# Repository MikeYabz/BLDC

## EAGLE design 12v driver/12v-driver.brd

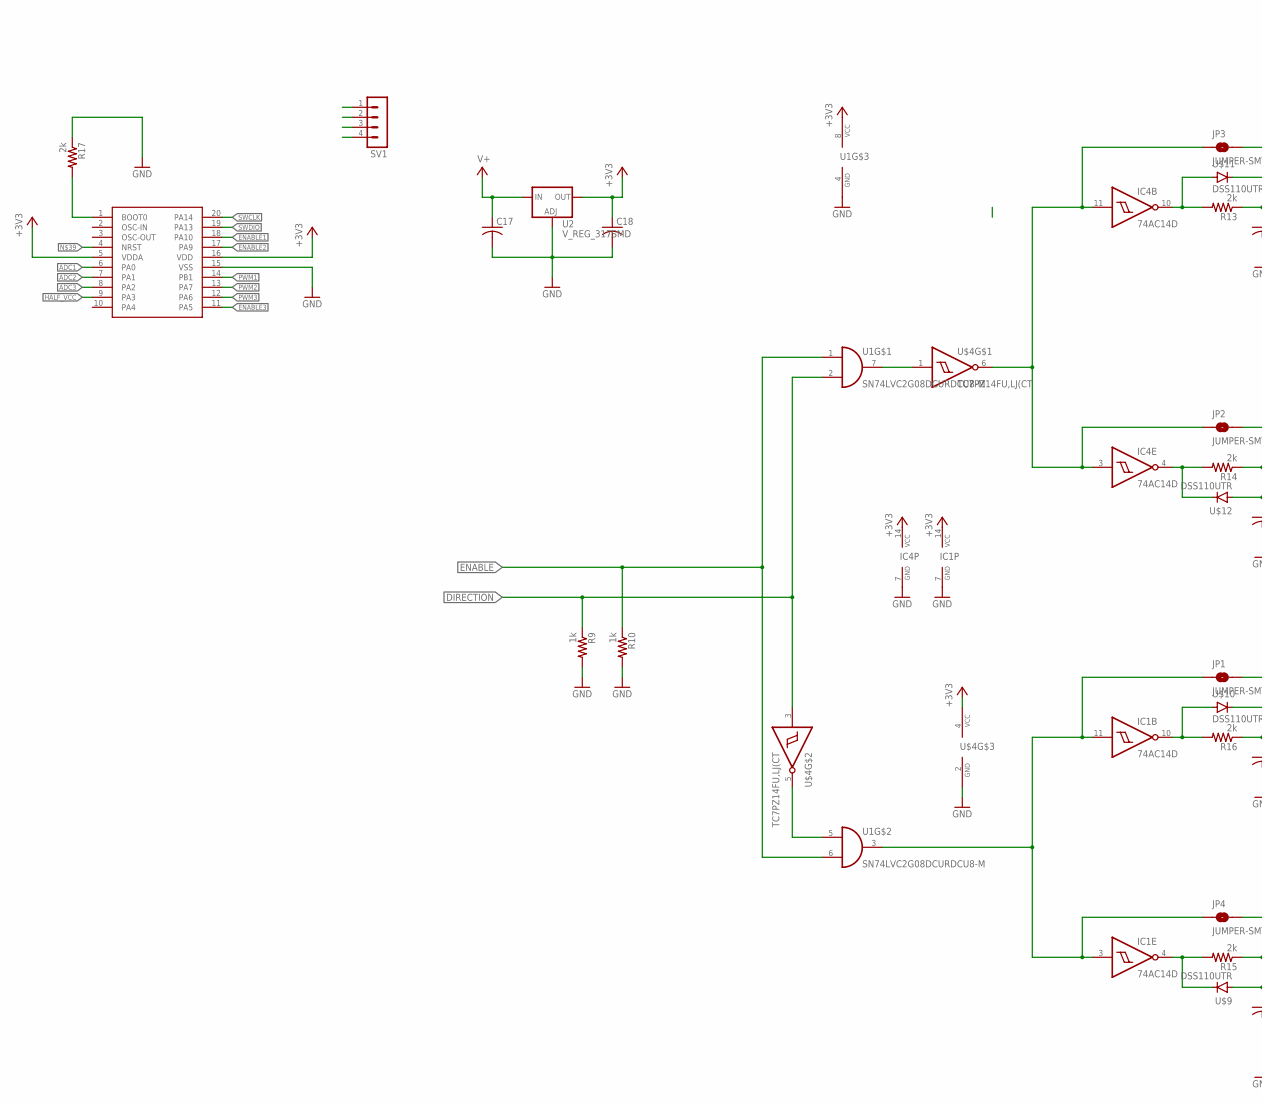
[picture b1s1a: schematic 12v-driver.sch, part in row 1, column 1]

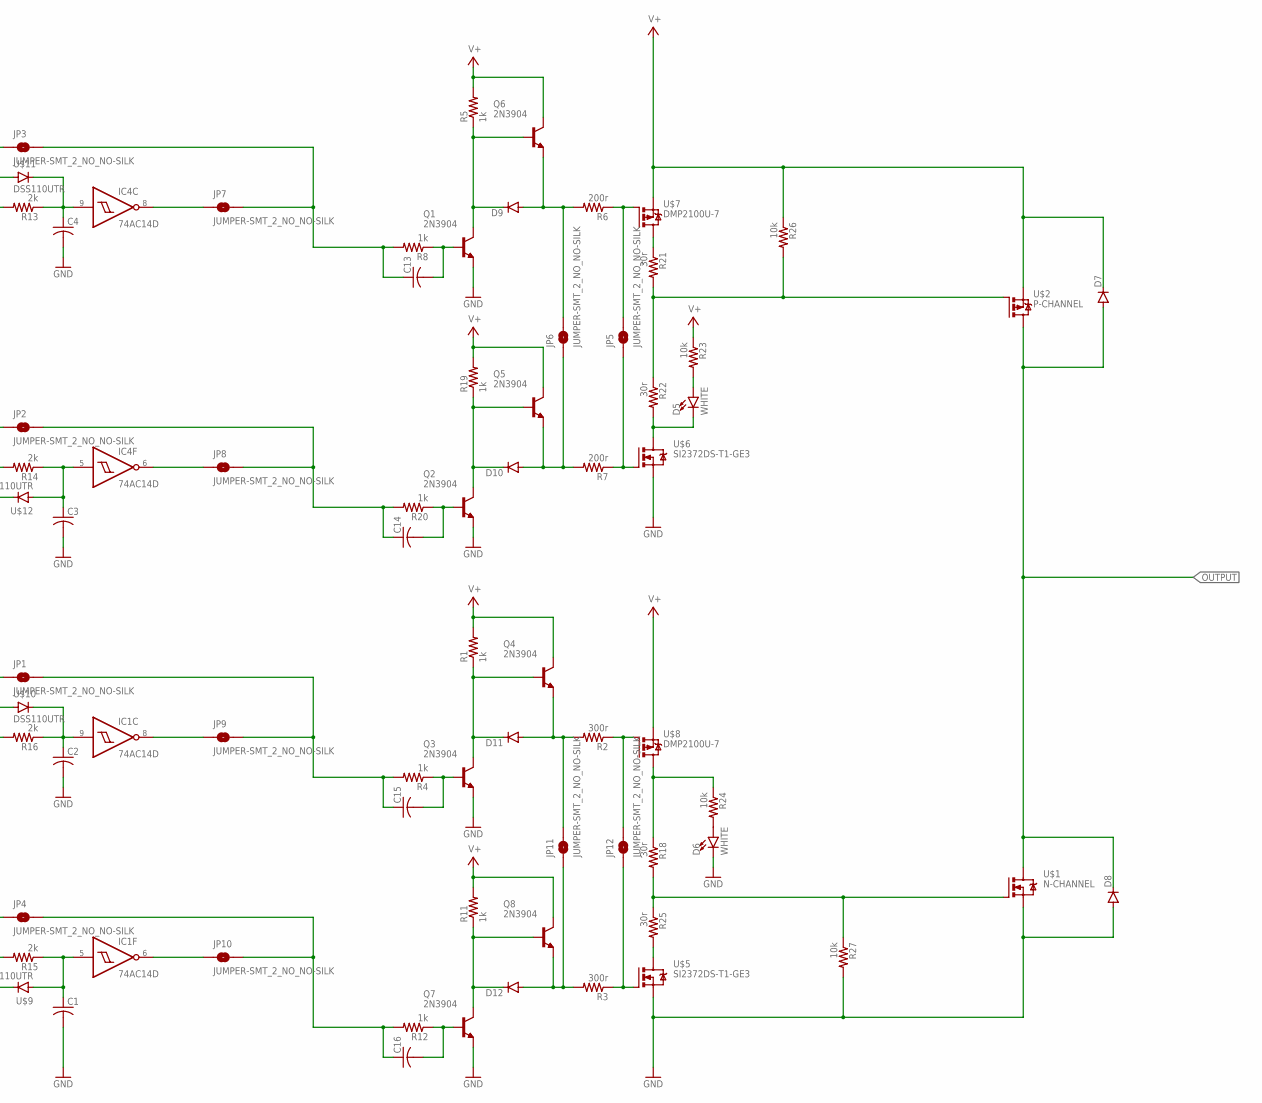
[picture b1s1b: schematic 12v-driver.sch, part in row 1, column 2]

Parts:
C1, C2, C3, C4, C13, C14, C15, C16: C-USC0603; C0603
C17, C18: C-US075-032X103; C075-032X103
D5, D6: WHITE; LED-1206
D7, D8, D9, D10, D11, D12: DIODE-DO-214AC; DO-214AC
IC1, IC4: 74AC14D; SO14
JP1, JP2, JP3, JP4, JP5, JP6, JP7, JP8, JP9, JP10, JP11, JP12: JUMPER-SMT_2_NO_NO-SILK; SMT-JUMPER_2_NO_NO-SILK
Q1, Q2, Q3, Q4, Q5, Q6, Q7, Q8: 2N3904; TO-92
R1, R4, R5, R8, R9, R10, R11, R12, R19, R20: 1k; R0603
R2, R3: 300r; R0603
R6, R7: 200r; R0603
R13, R14, R15, R16, R17: 2k; R0603
R18, R21, R22, R25: 30r; R0603
R23, R24, R26, R27: 10k; R0603
SV1: MA04-1
U1: SN74LVC2G08DCURDCU8-M; DCU8-M
U2: V_REG_317SMD; SOT223
U$1: N-CHANNEL; TO247BV
U$2: P-CHANNEL; TO247BV
U$3: STM32F070F6P6TR; TSSOP20
U$4: TC7PZ14FU,LJ(CT; SOT-363___(US6)
U$5, U$6: SI2372DS-T1-GE3; SOT-23
U$7, U$8: DMP2100U-7; SOT-23
U$9, U$10, U$11, U$12: DSS110UTR; SOD123FL

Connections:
+3V3: C18.1, IC1.14 (VCC), IC4.14 (VCC), U1.8 (VCC), U2.2 (OUT), U$3.5 (VDDA), U$3.16 (VDD), U$4.4 (VCC)
ADC1: U$3.6 (PA0)
ADC2: U$3.7 (PA1)
ADC3: U$3.8 (PA2)
DIRECTION: R9.1, U1.2 (I1), U$4.3 (I)
ENABLE: R10.1, U1.1 (I0), U1.6 (I1)
ENABLE1: U$3.18 (PA10)
ENABLE2: U$3.17 (PA9)
ENABLE3: U$3.11 (PA5)
GND: C1.2, C2.2, C3.2, C4.2, C17.2, C18.2, D6.C, D8.A, IC1.7 (GND), IC4.7 (GND), Q1.E, Q2.E, Q3.E, Q7.E, R9.2, R10.2, R17.1, R27.2, U1.4 (GND), U2.1 (ADJ), U$1.S, U$3.15 (VSS), U$4.2 (GND), U$5.2 (S), U$6.2 (S)
HALF_VCC: U$3.9 (PA3)
IN1: IC1.3 (I), IC1.11 (I), JP1.1, JP4.1, U1.3 (O)
IN2: IC4.3 (I), IC4.11 (I), JP2.1, JP3.1, U$4.6 (O)
unnamed: R18.2, R25.1, R27.1, U$1.G
unnamed: R17.2, U$3.1 (BOOT0)
unnamed: D11.C, Q3.C, Q4.B, R1.1
unnamed: JP12.2, R2.1, U$8.1 (G)
unnamed: JP12.1, R3.1, U$5.1 (G)
unnamed: C15.2, Q3.B, R4.1
unnamed: R21.2, R22.1, R26.2, U$2.G
unnamed: R18.1, R24.1, U$8.3 (D)
unnamed: D9.C, Q1.C, Q6.B, R5.1
unnamed: JP5.2, R6.1, U$7.1 (G)
unnamed: JP5.1, R7.1, U$6.1 (G)
unnamed: C13.2, Q1.B, R8.1
unnamed: IC1.10 (O), R16.2, U$10.A
unnamed: IC4.8 (O), JP7.1
unnamed: U1.5 (I0), U$4.5 (O)
unnamed: C2.1, IC1.9 (I), R16.1, U$10.C
unnamed: C15.1, JP1.2, JP9.2, R4.2
unnamed: C3.1, IC4.5 (I), R14.1, U$12.A
unnamed: IC4.6 (O), JP8.1
unnamed: C4.1, IC4.9 (I), R13.1, U$11.C
unnamed: C13.1, JP3.2, JP7.2, R8.2
unnamed: IC4.10 (O), R13.2, U$11.A
unnamed: IC4.4 (O), R14.2, U$12.C
unnamed: IC1.8 (O), JP9.1
unnamed: IC1.4 (O), R15.2, U$9.C
unnamed: C1.1, IC1.5 (I), R15.1, U$9.A
unnamed: IC1.6 (O), JP10.1
unnamed: C16.1, JP4.2, JP10.2, R12.2
unnamed: D5.A, R23.2
unnamed: D6.A, R24.2
unnamed: C16.2, Q7.B, R12.1
unnamed: D12.C, Q7.C, Q8.B, R11.1
unnamed: C14.2, Q2.B, R20.1
unnamed: C14.1, JP2.2, JP8.2, R20.2
unnamed: D10.C, Q2.C, Q5.B, R19.1
unnamed: U1.7 (O), U$4.1 (I)
unnamed: R21.1, U$7.3 (D)
unnamed: D5.C, R22.2, U$6.3 (D)
unnamed: R25.2, U$5.3 (D)
unnamed: D9.A, JP6.2, Q6.E, R6.2
unnamed: D10.A, JP6.1, Q5.E, R7.2
unnamed: D11.A, JP11.2, Q4.E, R2.2
unnamed: D12.A, JP11.1, Q8.E, R3.2
OUTPUT: D7.A, D8.C, U$1.D, U$2.D
PWM1: U$3.14 (PB1)
PWM2: U$3.13 (PA7)
PWM3: U$3.12 (PA6)
SWCLK: U$3.20 (PA14)
SWDIO: U$3.19 (PA13)
V+: C17.1, D7.C, Q4.C, Q5.C, Q6.C, Q8.C, R1.2, R5.2, R11.2, R19.2, R23.1, R26.1, U2.3 (IN), U$2.S, U$7.2 (S), U$8.2 (S)

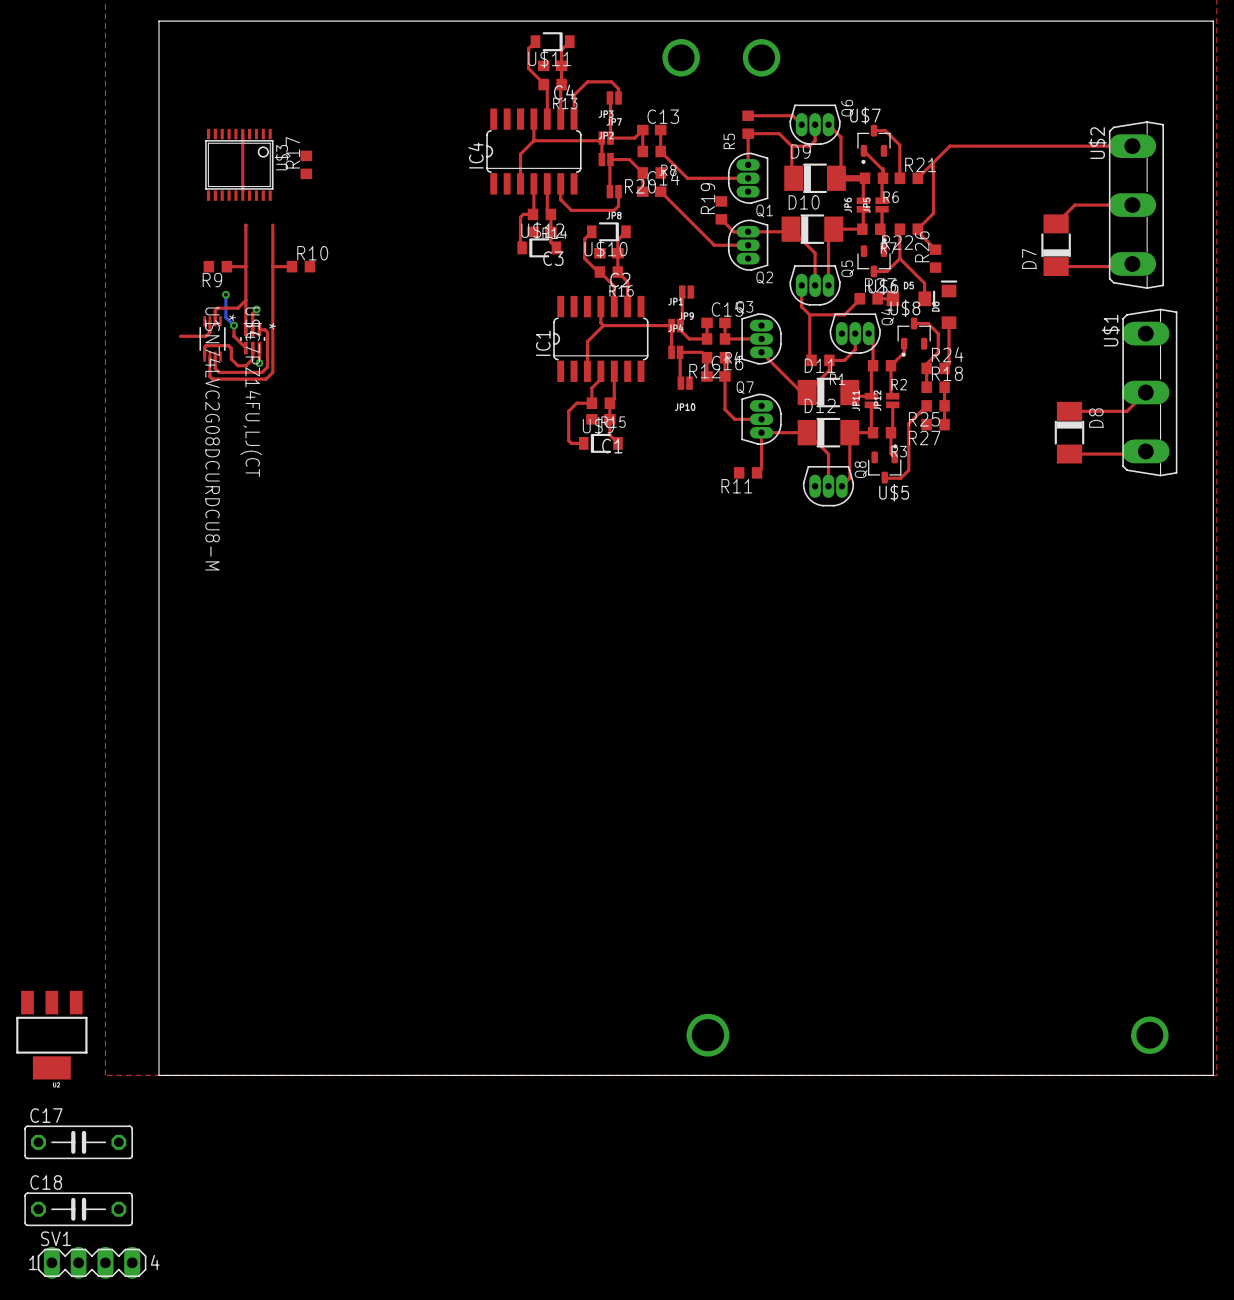
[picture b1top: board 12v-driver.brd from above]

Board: 2 copper layers, 100.0 x 100.0 mm, 82 parts (0 on the bottom side), 51 nets.

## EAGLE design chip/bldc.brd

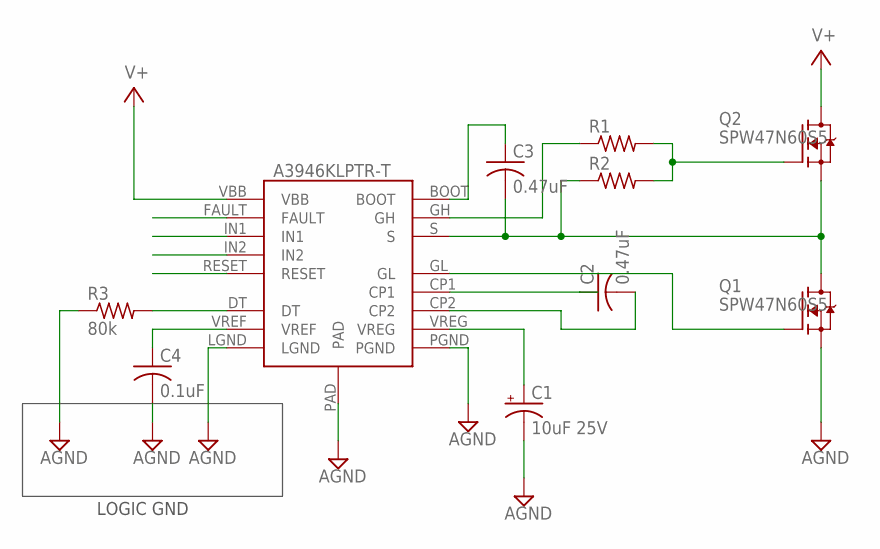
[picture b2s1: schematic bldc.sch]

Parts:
C1: 10uF 25V; 175TMP-0808
C2: 0.47uF; C0805
C3: 0.47uF; C050-030X075
C4: 0.1uF; C0805
Q1, Q2: SPW47N60S5; P-TO247
R1, R2: R-US_R0805; R0805
R3: 80k; R0805
U$1: A3946KLPTR-T; SOP65P640X120-17T300

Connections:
AGND: C1.-, C4.2, Q1.3 (S), R3.1, U$1.LGND, U$1.PAD, U$1.PGND
unnamed: C2.2, U$1.CP2
unnamed: C1.+, U$1.VREG
unnamed: C2.1, U$1.CP1
unnamed: Q1.1 (G), U$1.GL
unnamed: C3.2, Q1.2 (D), Q2.3 (S), R2.1, U$1.S
unnamed: C3.1, U$1.BOOT
unnamed: R1.1, U$1.GH
unnamed: Q2.1 (G), R1.2, R2.2
unnamed: C4.1, U$1.VREF
unnamed: R3.2, U$1.DT
V+: Q2.2 (D), U$1.VBB

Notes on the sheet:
LOGIC GND

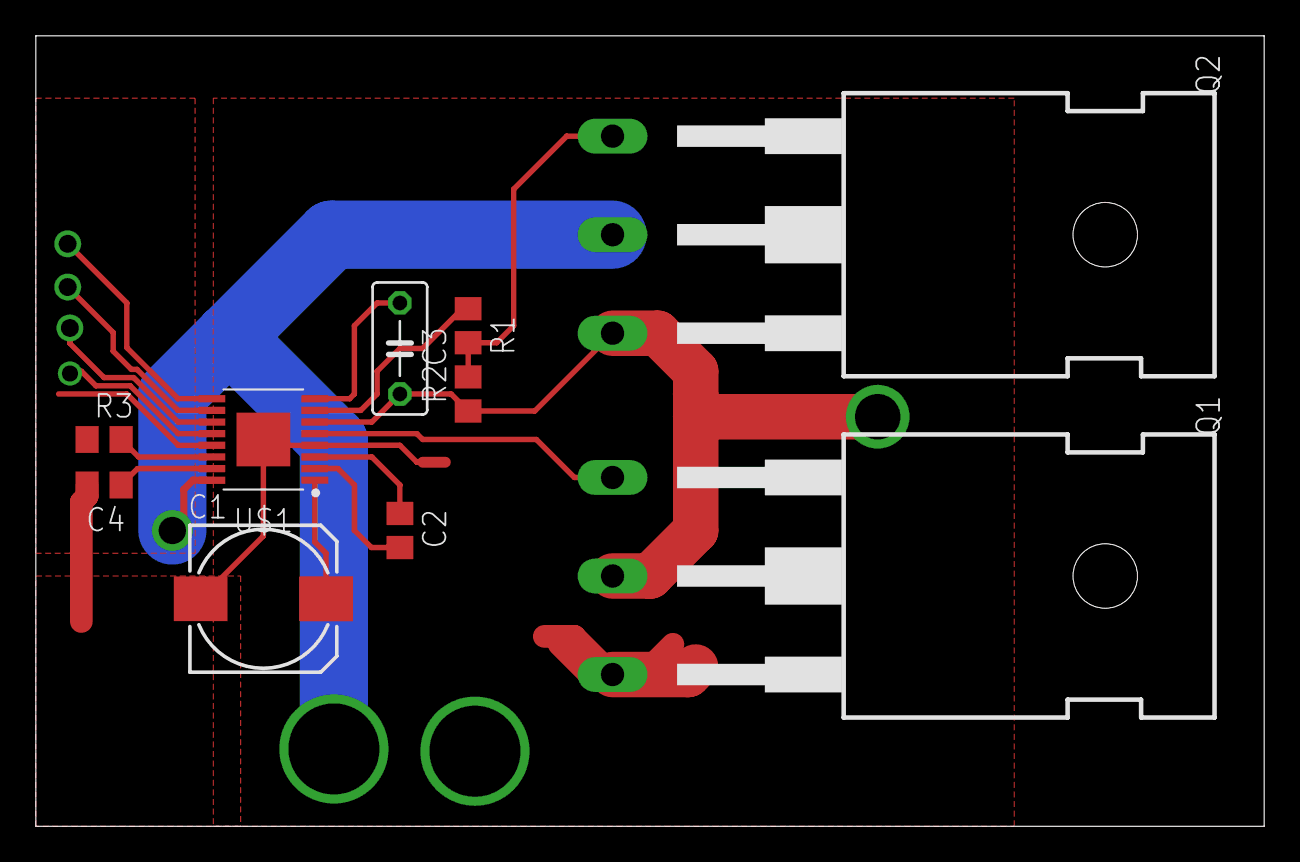
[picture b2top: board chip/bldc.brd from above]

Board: 2 copper layers, 68.6 x 44.1 mm, 10 parts (0 on the bottom side), 12 nets.

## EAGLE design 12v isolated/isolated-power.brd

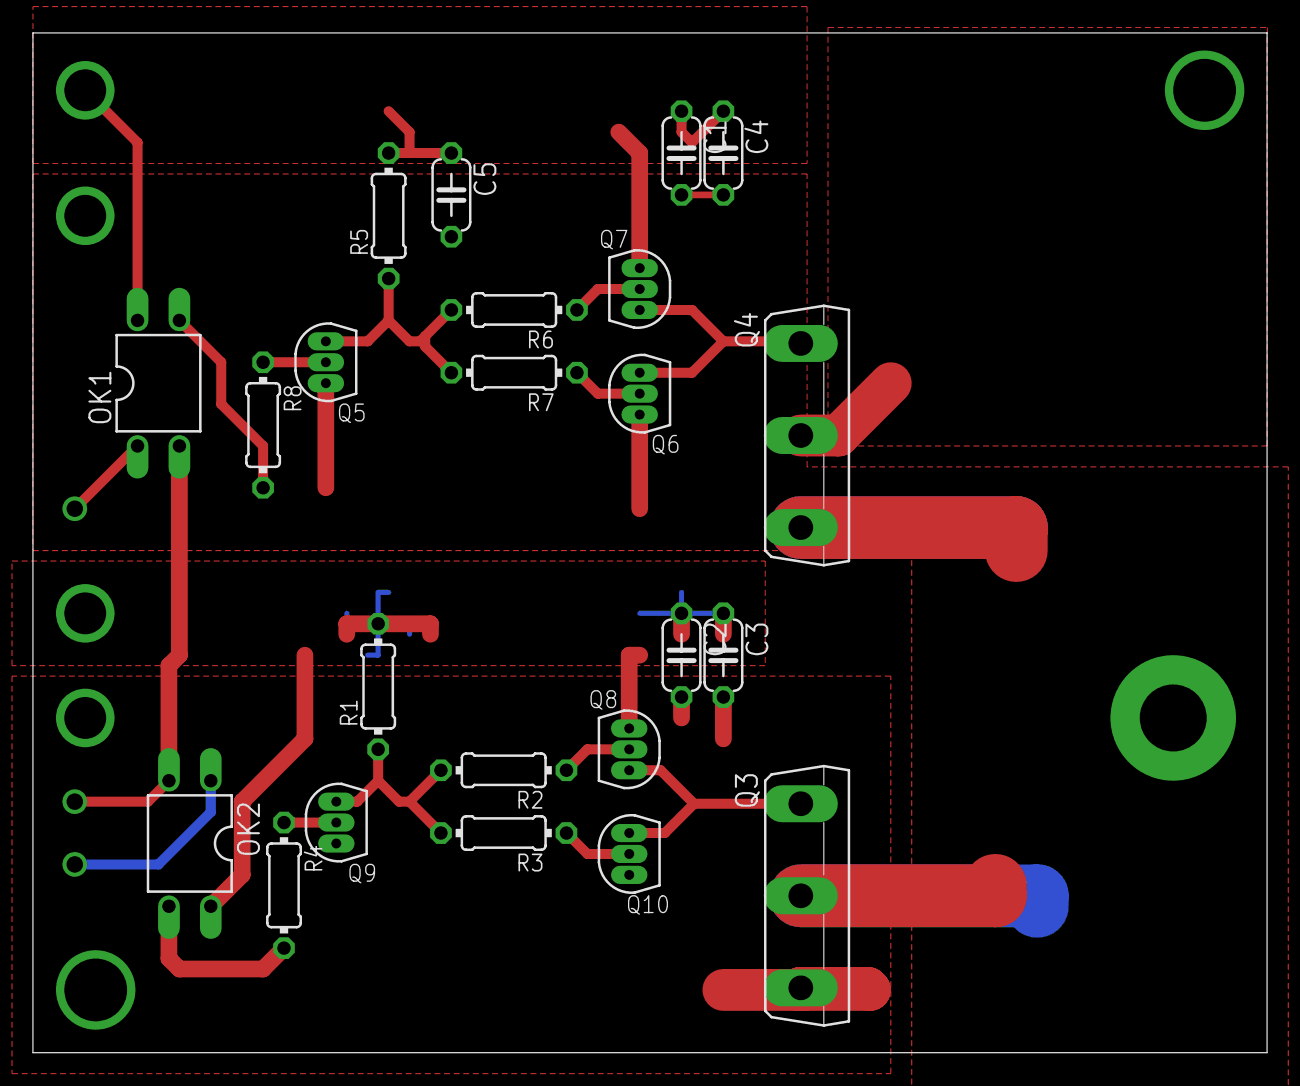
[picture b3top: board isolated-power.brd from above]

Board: 2 copper layers, 74.9 x 61.9 mm, 23 parts (0 on the bottom side), 17 nets.

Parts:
C1, C2: 0.1u; C050-024X044
C3, C4: 1u; C050-024X044
C5: C050-024X044
OK1, OK2: LTV816; DIL04
Q3, Q4: IRFPC40; TO247BV
Q5, Q6, Q9, Q10: 2N3904; TO-92
Q7, Q8: 2N3906; TO-92
R1, R8: 1k; 0204/7
R2, R3, R4: 0204/7
R5, R6, R7: 500r; 0204/7

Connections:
12V-HIGH: C1.1, C4.1, C5.1, OK1.4, Q7.E, R5.2
12V-LOW: C2.1, C3.1, OK2.4, Q8.E, R1.2
GND: C2.2, C3.2, Q3.S, Q9.E, Q10.E
GND1: OK1.2, OK2.2
MOTOR_OUT: C1.2, C4.2, C5.2, Q3.D, Q4.S, Q5.E, Q6.E
unnamed: Q3.G, Q8.C, Q10.C
unnamed: Q9.C, R1.1, R2.2, R3.2
unnamed: OK1.3, R8.2
unnamed: Q8.B, R2.1
unnamed: Q10.B, R3.1
unnamed: Q9.B, R4.1
unnamed: Q4.G, Q6.C, Q7.C
unnamed: Q5.C, R5.1, R6.2, R7.2
unnamed: OK2.3, R4.2
unnamed: Q7.B, R6.1
unnamed: Q6.B, R7.1
unnamed: Q5.B, R8.1

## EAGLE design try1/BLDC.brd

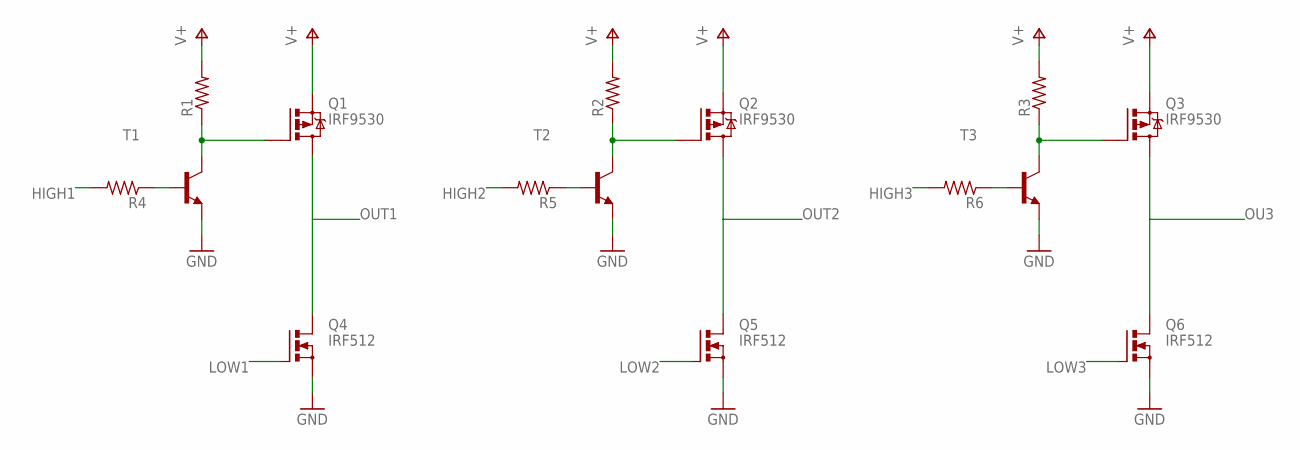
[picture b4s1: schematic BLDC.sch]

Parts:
Q1, Q2, Q3: IRF9530; TO220BV
Q4, Q5, Q6: IRF512; TO220BV
R1, R2, R3, R4, R5, R6: R-US_0204/7; 0204/7
T1, T2, T3: -NPN-TO92-BEC; TO92-BEC

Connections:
GND: Q4.S, Q5.S, Q6.S, T1.E, T2.E, T3.E
HIGH1: R4.2
HIGH2: R5.2
HIGH3: R6.2
LOW1: Q4.G
LOW2: Q5.G
LOW3: Q6.G
unnamed: Q2.G, R2.1, T2.C
unnamed: Q1.G, R1.1, T1.C
unnamed: Q3.G, R3.1, T3.C
unnamed: R4.1, T1.B
unnamed: R5.1, T2.B
unnamed: R6.1, T3.B
OU3: Q3.D, Q6.D
OUT1: Q1.D, Q4.D
OUT2: Q2.D, Q5.D
V+: Q1.S, Q2.S, Q3.S, R1.2, R2.2, R3.2

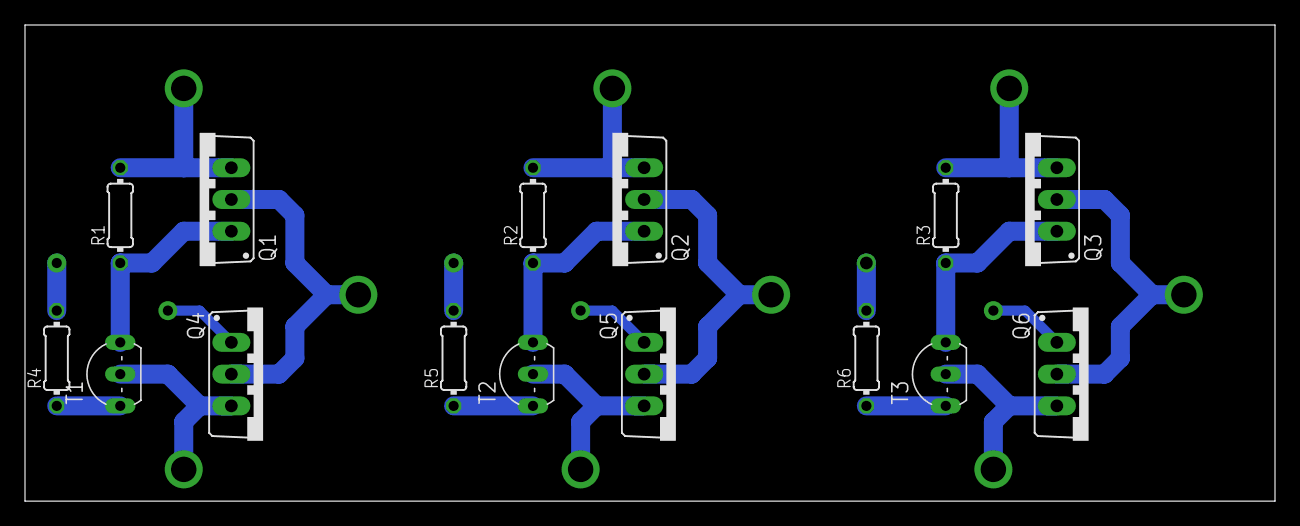
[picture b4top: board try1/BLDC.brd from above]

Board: 2 copper layers, 100.0 x 38.1 mm, 15 parts (0 on the bottom side), 11 nets.

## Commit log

2019-08-06 added new circuit
2019-10-02 updated board
2019-10-03 added new circuits
2019-10-08 production files
2020-01-14 12driver fix inversion and SMD
2020-01-17 added inverter to driver NPNs
2020-01-21 fixed production problems
2020-02-17 started rework of new schematic
2020-02-19 started routing v2
2020-02-19 made panel
2020-02-19 DRC good

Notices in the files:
parts and their libraries:
SparkFun-LED: Licensing: Creative Commons ShareAlike 4.0 International - https://creativecommons.org/licenses/by-sa/4.0
